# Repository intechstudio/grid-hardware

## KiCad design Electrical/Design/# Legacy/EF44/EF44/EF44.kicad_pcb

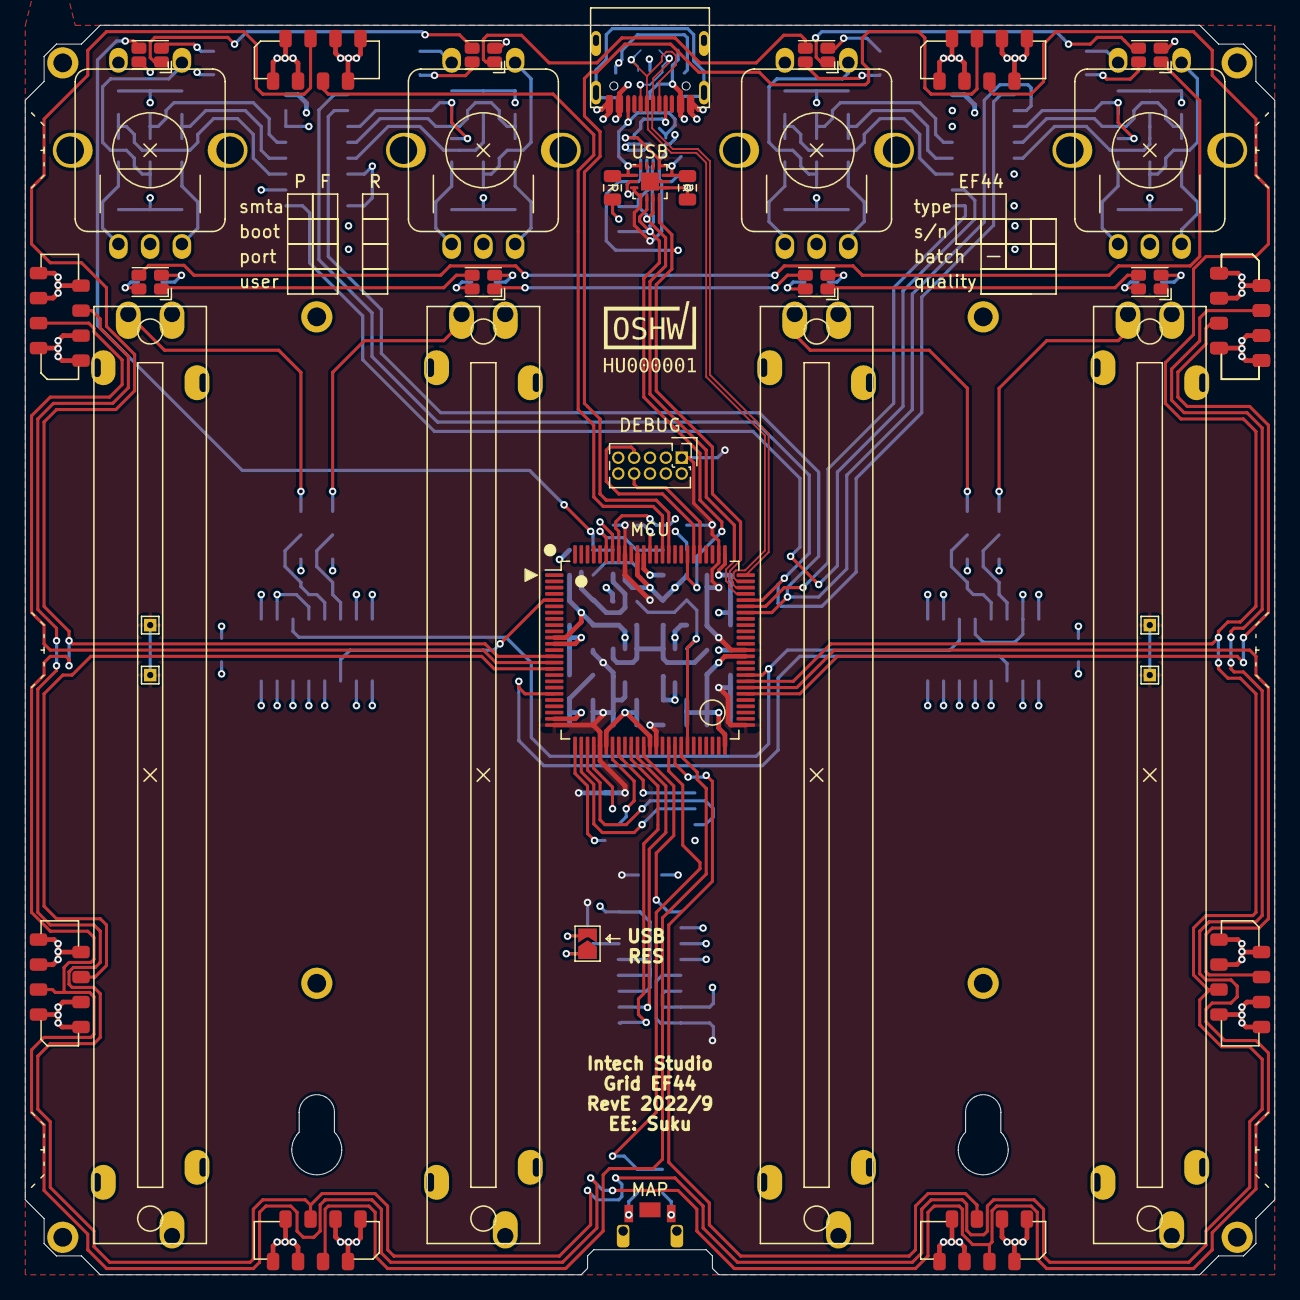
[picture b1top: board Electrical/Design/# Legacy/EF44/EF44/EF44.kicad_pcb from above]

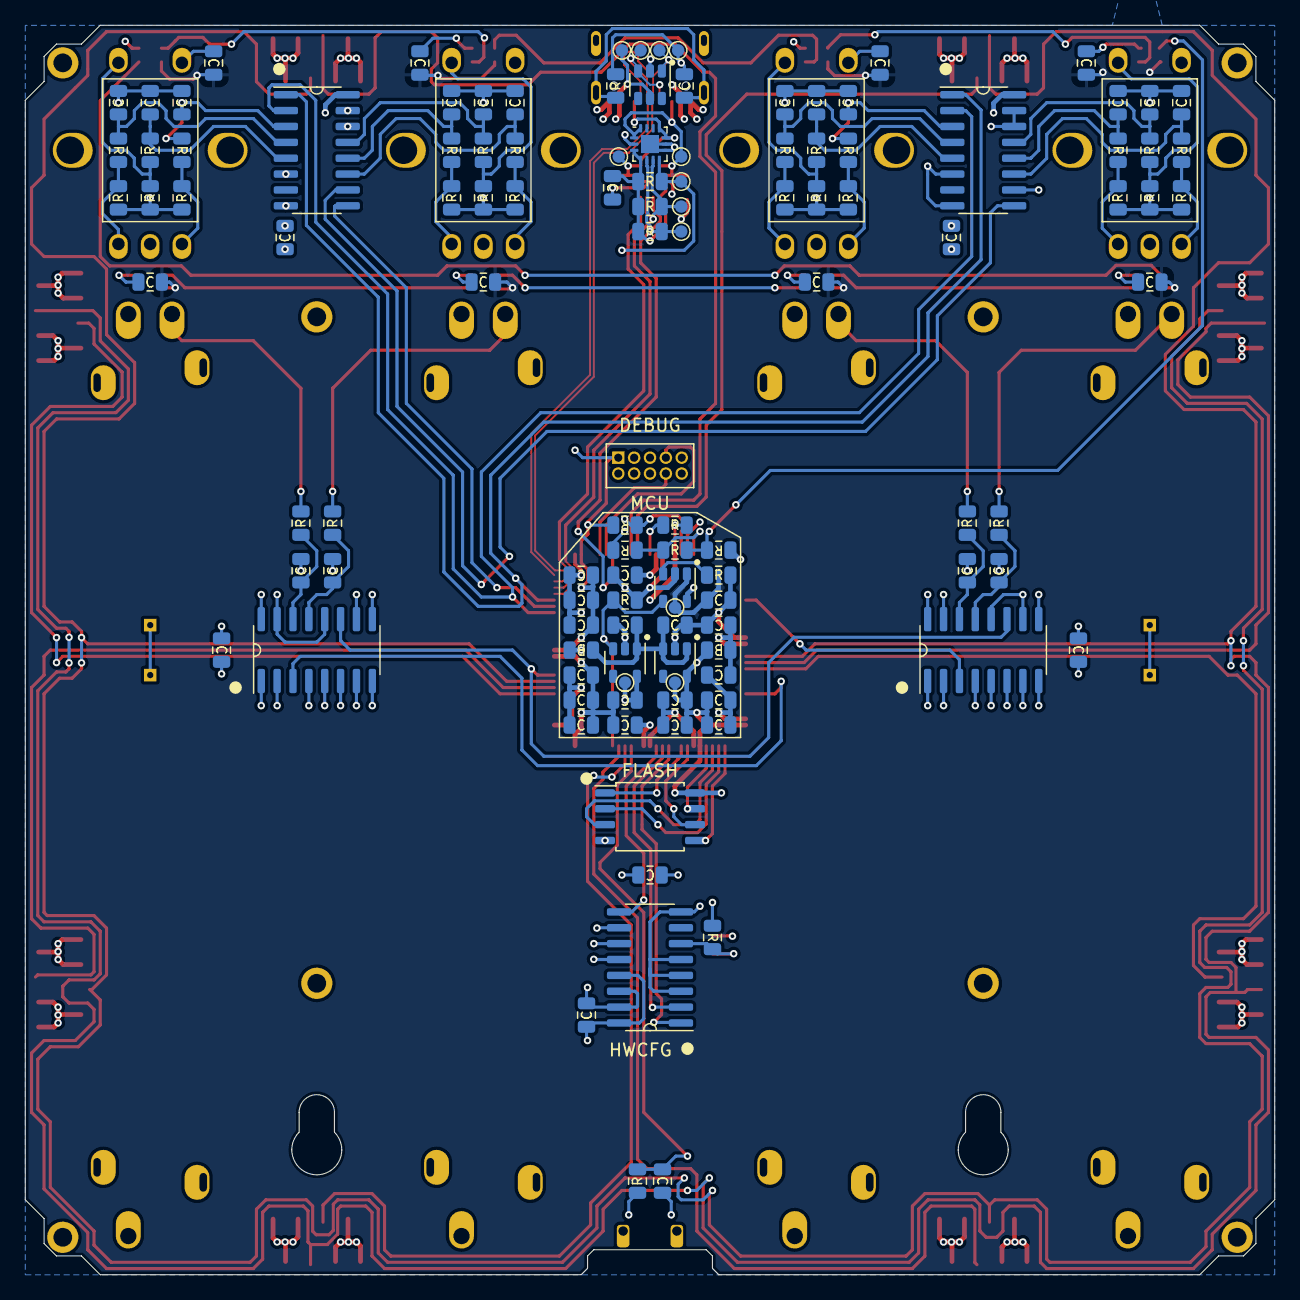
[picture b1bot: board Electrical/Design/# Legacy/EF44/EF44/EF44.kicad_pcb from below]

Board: 4 copper layers, 100.0 x 100.0 mm, 156 parts (117 on the bottom side), 94 nets.

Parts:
C1, C2, C3, C4, C5, C6, C7, C8, C9, C10, C11, C12, C13, C14, C17, C18, C19, C20, C21, C22, C23, C24, C25, C26, C27, C28, C33, C39, C41, C42, C44, C45, C46, C47, C48, C49, C51, C54, C55, C86, C87, C94, C95: 100n; CAP_0805
C34, C36, C40, C50, C53: 1u; CAP_0805
C37: 4n7; CAP_0805
C38, C43: 10u; CAP_0805
D1, D2, D3, D4, D5, D6, D7, D8: WS2812C-2020; UI_WS2812C-2020
J1: USB_C_TYPE-C-32-M-12; USB_C_Korean_Hroparts_TYPE-C-31-M-12
J2: (NF); PinHeader_2x05_P1.27mm_Vertical
J4, J5, J6, J7, J7#2, J8, J9, J10, J11: TE Connectivity 84982-8; grid_ffc_8_vertical_smd
JP2: (NF); SolderJumper-2_P1.3mm_Open_TrianglePad1.0x1.5mm
L1, L2: GZ2012D601TF; FERRIT_0805
LOGO1: OSHWA
M1: (NF); grid_outline
R1, R2, R3, R4, R5, R6, R7, R8, R9, R10, R11, R12, R13, R14, R15, R16, R17, R18, R19, R20, R21, R22, R23, R24, R36, R111, R112: 10k; RES_0805
R25, R26, R27, R28, R38, R39, R40, R41, R42: 1k; RES_0805
R34, R37, R107, R108, R109, R110: 5k1; RES_0805
R35: 1M; RES_0805
SW1: C255807; SW_HYP_MAPMODE
TP1, TP2, TP3, TP4: TestPoint; TestPoint_THTPad_1.0x1.0mm_Drill0.5mm
TP5: D-; TestPoint_Pad_D1.0mm
TP6: D+; TestPoint_Pad_D1.0mm
TP7: GND; TestPoint_Pad_D1.0mm
TP8: VB; TestPoint_Pad_D1.0mm
TP9: UC; TestPoint_Pad_D1.0mm
TP10: UI; TestPoint_Pad_D1.0mm
TP11: UI_5V; TestPoint_Pad_D1.0mm
TP16: SDA; TestPoint_Pad_D1.0mm
TP17: SCL; TestPoint_Pad_D1.0mm
TP18: INT; TestPoint_Pad_D1.0mm
TP19: CC1; TestPoint_Pad_D1.0mm
TP20: CC2; TestPoint_Pad_D1.0mm
U1, U2, U3: 74HC165; SOIC-16_74HC165
U4: SESRV05-4; SOT-23-6
U5, U6: LN1134A332MR-G; SOT-23-5
U7: SAMD51N20A; TQFP-100_14x14mm_P0.5mm
U8: W25Q16JVSSIQ; SOIC-8W_FLASH
U9, U10: 74HC4051; SOIC-16_74HC4051
U15, U16: FUSB302BMPX (NF); WQFN-14-1EP_2.5x2.5mm_P0.5mm_EP1.45x1.45mm
U17: MT9700; SOT-23-5
UI1, UI2, UI3, UI4: EN12-HS22AF20 (NF); UI_ENCODER_TT
UI5, UI6, UI7, UI8: PS60-10MC1BR10K (NF); UI_FADER_TT_long

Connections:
+3V3_UC: C33.1, C40.1, C41.1, C42.1, C43.1, C44.1, C45.1, C46.1, C47.1, C48.1, C51.1, C54.1, C55.1, C94.1, J2.1, L1.2, R38.2, R39.2, R108.1, R109.1, R110.1, R112.1, TP1.1, TP2.1, TP3.1, TP4.1, TP9.1, U3.13 (D2), U3.16 (VCC), U5.5 (OUT), U7.25 (VDDIOB0), U7.30 (VDDIOB1), U7.39 (VDDIO0), U7.51 (VDDIO1), U7.63 (VDDIO2), U7.77 (VDDIO3), U7.92 (VDDIO4), U8.8 (VCC), U15.3 (VDD), U15.4 (VDD), U16.3 (VDD), U16.4 (VDD)
+3V3_UI: C13.1, C14.1, C36.1, C86.1, C87.1, R1.1, R2.1, R3.1, R7.1, R8.1, R9.1, R13.1, R14.1, R15.1, R19.1, R20.1, R21.1, TP10.1, U1.16 (VCC), U2.16 (VCC), U6.5 (OUT), U9.16 (VDD), U10.16 (VDD), UI5.1, UI6.1, UI7.1, UI8.1
+5V: J1.A4B9 (VBUS), J1.A9B4 (VBUS), J4.6, J4.7, J4.8, J5.1, J5.2, J5.3, J6.1, J6.2, J6.3, J7.6, J7.7, J7.8, J7#2.6, J7#2.7, J7#2.8, J8.6, J8.7, J8.8, J9.1, J9.2, J9.3, J10.1, J10.2, J10.3, J11.6, J11.7, J11.8, L2.2, R34.1, TP8.1, U4.5, U15.2 (VBUS), U16.2 (VBUS), U17.5 (IN)
+5V_UI: C1.2, C2.2, C3.2, C4.2, C5.2, C6.2, C7.2, C8.2, C50.1, D1.4 (VDD), D2.4 (VDD), D3.4 (VDD), D4.4 (VDD), D5.4 (VDD), D6.4 (VDD), D7.4 (VDD), D8.4 (VDD), TP11.1, U17.1 (OUT)
/HWCFG/HWCFG_CLOCK: U3.2 (CLK), U7.36 (PB14)
/HWCFG/HWCFG_DATA: U3.9 (Q), U7.37 (PB15)
/HWCFG/HWCFG_SHIFT: U3.1 (SH/~LD), U7.35 (PB13)
/MCU/GRID_AUX_RX: J2.8, U7.80 (PB24)
/MCU/GRID_AUX_TX: J2.7, U7.81 (PB25)
/MCU/GRID_EAST_RX: J7.5, J7#2.5, U7.56 (PC16)
/MCU/GRID_EAST_TX: J9.4, U7.57 (PC17)
/MCU/GRID_NORTH_RX: J4.5, U7.86 (PC28)
/MCU/GRID_NORTH_TX: J5.4, U7.85 (PC27)
/MCU/GRID_SOUTH_RX: J11.5, U7.42 (PC12)
/MCU/GRID_SOUTH_TX: J10.4, U7.43 (PC13)
/MCU/GRID_SYNC_1: J5.5, J6.5, J9.5, J10.5, U7.58 (PC18)
/MCU/GRID_SYNC_2: J4.4, J7.4, J7#2.4, J8.4, J11.4, U7.14 (PB07)
/MCU/GRID_WEST_RX: J8.5, U7.16 (PB09)
/MCU/GRID_WEST_TX: J6.4, U7.15 (PB08~)
/MCU/LED_DATA_OUT: D1.3 (DIN), R34.2, R42.2
/MCU/MAP_MODE: C95.1, R40.2, U7.41 (PC11)
/MCU/MUX_ADDRESS_A: U7.59 (PC19), U9.11 (A), U10.11 (A)
/MCU/MUX_OUT_1: U7.5 (PC02), U9.3 (X)
/MCU/MUX_OUT_2: U7.20 (PA07), U10.3 (X)
/MCU/QSPI_IO_0: U7.26 (PA08), U8.5 (DI(IO0))
/MCU/QSPI_IO_1: U7.27 (PA09), U8.2 (DO(IO1))
/MCU/QSPI_IO_2: U7.28 (PA10), U8.3 (IO2)
/MCU/QSPI_IO_3: U7.29 (PA11), U8.7 (IO3)
/MCU/QSPI_SCK: U7.32 (PB10), U8.6 (CLK)
/MCU/QSPI_~CE: U7.33 (PB11), U8.1 (~CS)
/MCU/SYS_I2C_INT_0: R110.2, TP18.1, U7.82 (PC24), U15.5 (INT_N), U16.5 (INT_N)
/MCU/SYS_I2C_SCL: R109.2, TP17.1, U7.72 (PA22), U15.6 (SCL), U16.6 (SCL)
/MCU/SYS_I2C_SDA: R108.2, TP16.1, U7.73 (PA23), U15.7 (SDA), U16.7 (SDA)
/MCU/SYS_RESET: J2.10, R38.1, U7.88 (~RESET)
/MCU/SYS_SWCLK: J2.4, R39.1, U7.93 (PA30)
/MCU/SYS_SWDIO: J2.2, U7.94 (PA31)
/MCU/SYS_SWO: J2.6, R41.2
/MCU/Sheet60FB6C45/USB_CC1: J1.A5 (CC1), R37.1, TP19.1, U15.10 (CC1), U15.11 (CC1), U16.10 (CC1), U16.11 (CC1)
/MCU/Sheet60FB6C45/USB_CC2: J1.B5 (CC2), R107.1, TP20.1, U15.1 (CC2), U15.14 (CC2), U16.1 (CC2), U16.14 (CC2)
/MCU/UI_PWR_EN: R36.1, U6.3 (EN), U7.44 (PC14), U17.4 (ON)
/MCU/USB_DN: J1.A7 (D-), J1.B7 (D-), TP5.1, U4.1, U7.74 (PA24)
/MCU/USB_DP: J1.A6 (D+), J1.B6 (D+), TP6.1, U4.3, U7.75 (PA25)
/UI_ENC/CLOCK: U1.2 (CLK), U2.2 (CLK), U7.69 (PB21)
/UI_ENC/DATA: U2.9 (Q), U7.70 (PA20)
/UI_ENC/ENCODER_1/A: C19.1, R6.1, U1.11 (D0)
/UI_ENC/ENCODER_1/B: C18.1, R5.1, U1.12 (D1)
/UI_ENC/ENCODER_1/C: C17.1, R4.2, U1.13 (D2)
/UI_ENC/ENCODER_2/A: C22.1, R12.1, U1.3 (D4)
/UI_ENC/ENCODER_2/B: C21.1, R11.1, U1.4 (D5)
/UI_ENC/ENCODER_2/C: C20.1, R10.2, U1.5 (D6)
/UI_ENC/ENCODER_3/A: C25.1, R18.1, U2.11 (D0)
/UI_ENC/ENCODER_3/B: C24.1, R17.1, U2.12 (D1)
/UI_ENC/ENCODER_3/C: C23.1, R16.2, U2.13 (D2)
/UI_ENC/ENCODER_4/A: C28.1, R24.1, U2.3 (D4)
/UI_ENC/ENCODER_4/B: C27.1, R23.1, U2.4 (D5)
/UI_ENC/ENCODER_4/C: C26.1, R22.2, U2.5 (D6)
/UI_ENC/SHIFT: U1.1 (SH/~LD), U2.1 (SH/~LD), U7.71 (PA21)
GND: C1.1, C2.1, C3.1, C4.1, C5.1, C6.1, C7.1, C8.1, C9.2, C10.2, C11.2, C12.2, C13.2, C14.2, C17.2, C18.2, C19.2, C20.2, C21.2, C22.2, C23.2, C24.2, C25.2, C26.2, C27.2, C28.2, C33.2, C34.2, C36.2, C37.2, C38.2, C39.2, C40.2, C41.2, C42.2, C43.2, C44.2, C45.2, C46.2, C47.2, C48.2, C49.2, C50.2, C51.2, C53.2, C54.2, C55.2, C86.2, C87.2, C94.2, C95.2, D1.2 (VSS), D2.2 (VSS), D3.2 (VSS), D4.2 (VSS), D5.2 (VSS), D6.2 (VSS), D7.2 (VSS), D8.2 (VSS), J1.A1B12 (GND), J1.A12B1 (GND), J2.3, J2.5, J2.9, J4.1, J4.2, J4.3, J5.6, J5.7, J5.8, J6.6, J6.7, J6.8, J7.1, J7.2, J7.3, J7#2.1, J7#2.2, J7#2.3, J8.1, J8.2, J8.3, J9.6, J9.7, J9.8, J10.6, J10.7, J10.8, J11.1, J11.2, J11.3, JP2.2 (B), R35.2, R36.2, R37.2, R107.2, R111.2, SW1.2 (B), TP7.1, U1.6 (D7), U1.8 (GND), U1.10 (SI), U1.14 (D3), U1.15 (INH), U2.6 (D7), U2.8 (GND), U2.14 (D3), U2.15 (INH), U3.3 (D4), U3.4 (D5), U3.5 (D6), U3.8 (GND), U3.10 (SI), U3.11 (D0), U3.12 (D1), U3.14 (D3), U3.15 (INH), U4.2, U5.2 (GND), U6.2 (GND), U7.11 (GNDANA), U7.24 (GNDIOB0), U7.31 (GNDIOB0), U7.38 (GND0), U7.50 (GND1), U7.62 (GND2), U7.76 (GND3), U7.90 (GND4), U8.4 (GND), U9.1 (X4), U9.2 (X6), U9.4 (X7), U9.5 (X5), U9.6 (Inh), U9.7 (VEE), U9.8 (VSS), U9.9 (C), U9.10 (B), U9.12 (X3), U9.15 (X2), U10.1 (X4), U10.2 (X6), U10.4 (X7), U10.5 (X5), U10.6 (Inh), U10.7 (VEE), U10.8 (VSS), U10.9 (C), U10.10 (B), U10.12 (X3), U10.15 (X2), U15.8 (GND), U15.9 (GND), U15.15 (GND), U16.8 (GND), U16.9 (GND), U16.15 (GND), U17.2 (GND), UI1.2, UI1.4, UI2.2, UI2.4, UI3.2, UI3.4, UI4.2, UI4.4, UI5.3, UI6.3, UI7.3, UI8.3
unnamed: C9.1, R25.1, U9.13 (X0)
unnamed: C10.1, R26.1, U10.13 (X0)
unnamed: C11.1, R27.1, U9.14 (X1)
unnamed: C12.1, R28.1, U10.14 (X1)
unnamed: C34.1, C53.1, L2.1, U5.1 (IN), U5.3 (EN), U6.1 (IN)
unnamed: C37.1, J1.S1 (SHIELD), J1.S2 (SHIELD), R35.1
unnamed: C38.1, C39.1, L1.1, U7.12 (VDDANA)
unnamed: C49.1, U7.89 (VDDCORE)
unnamed: D1.1 (DOUT), D2.3 (DIN)
unnamed: D2.1 (DOUT), D3.3 (DIN)
unnamed: D3.1 (DOUT), D4.3 (DIN)
unnamed: D4.1 (DOUT), D5.3 (DIN)
unnamed: D5.1 (DOUT), D6.3 (DIN)
unnamed: D6.1 (DOUT), D7.3 (DIN)
unnamed: D7.1 (DOUT), D8.3 (DIN)
unnamed: JP2.1 (A), R112.2, U3.6 (D7)
unnamed: R1.2, R4.1, UI1.5
unnamed: R2.2, R5.2, UI1.3
unnamed: R3.2, R6.2, UI1.1
unnamed: R7.2, R10.1, UI2.5
unnamed: R8.2, R11.2, UI2.3
unnamed: R9.2, R12.2, UI2.1
unnamed: R13.2, R16.1, UI3.5
unnamed: R14.2, R17.2, UI3.3
unnamed: R15.2, R18.2, UI3.1
unnamed: R19.2, R22.1, UI4.5
unnamed: R20.2, R23.2, UI4.3
unnamed: R21.2, R24.2, UI4.1
unnamed: R25.2, UI5.2
unnamed: R26.2, UI7.2
unnamed: R27.2, UI6.2
unnamed: R28.2, UI8.2
unnamed: R40.1, SW1.1 (A)
unnamed: R41.1, R42.1, U7.95 (PB30)
unnamed: R111.1, U17.3 (SET)
unnamed: U1.9 (Q), U2.10 (SI)

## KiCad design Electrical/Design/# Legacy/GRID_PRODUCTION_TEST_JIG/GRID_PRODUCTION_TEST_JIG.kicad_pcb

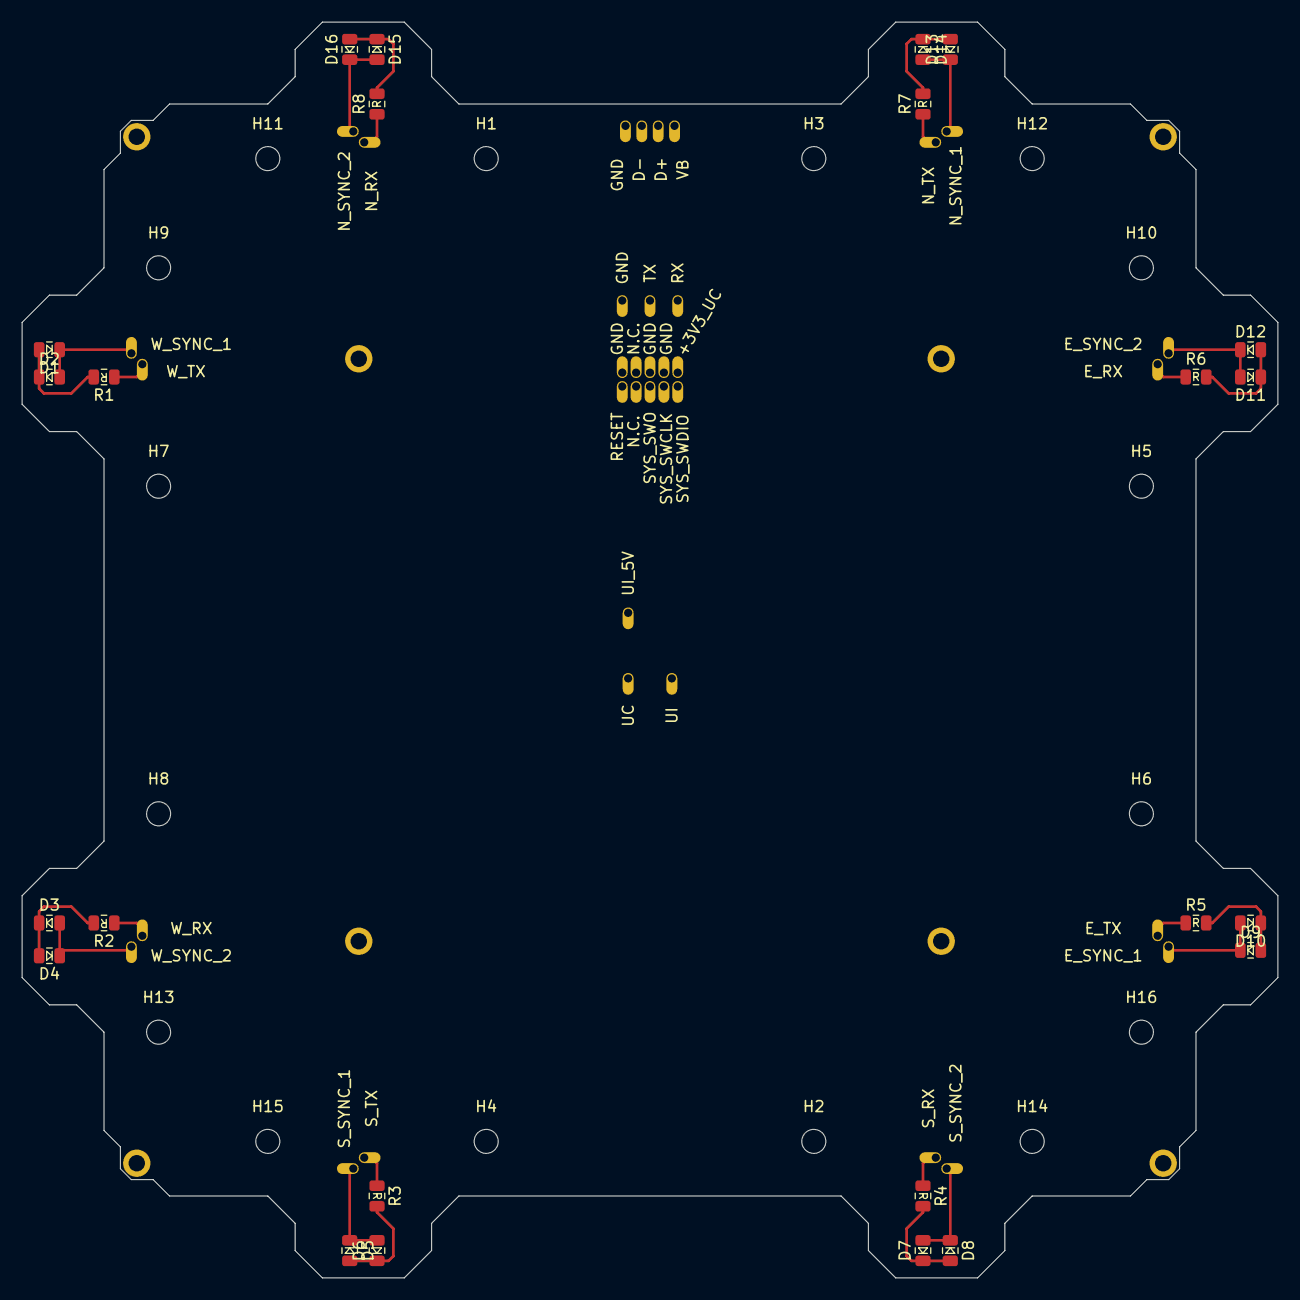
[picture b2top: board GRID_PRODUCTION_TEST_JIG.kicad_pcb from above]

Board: 2 copper layers, 115.0 x 115.0 mm, 77 parts (0 on the bottom side), 24 nets.

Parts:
D1, D2, D3, D4, D5, D6, D7, D8, D9, D10, D11, D12, D13, D14, D15, D16: LED; LED_0805
H1, H2, H3, H4, H5, H6, H7, H8, H9, H10, H11, H12, H13, H14, H15, H16: MountingHole; MountingHole_2.2mm_M2
M1: Conn_01x08; grid_outline
R1, R2, R3, R4, R5, R6, R7, R8: 1k; RES_0805
TP1: +3V3_UC; testpoint_pogo_0.75mm
TP2, TP3, TP5, TP11, TP18: GND; testpoint_pogo_0.75mm
TP4, TP9: N.C.; testpoint_pogo_0.75mm
TP6: SYS_SWDIO; testpoint_pogo_0.75mm
TP7: SYS_SWCLK; testpoint_pogo_0.75mm
TP8: SYS_SWO; testpoint_pogo_0.75mm
TP10: RESET; testpoint_pogo_0.75mm
TP12: VB; testpoint_pogo_0.75mm
TP13: D-; testpoint_pogo_0.75mm
TP14: D+; testpoint_pogo_0.75mm
TP15: UC; testpoint_pogo_0.75mm
TP16: UI; testpoint_pogo_0.75mm
TP17: UI_5V; testpoint_pogo_0.75mm
TP19: TX; testpoint_pogo_0.75mm
TP20: RX; testpoint_pogo_0.75mm
TP21: W_SYNC_1; testpoint_pogo_0.75mm
TP22: W_TX; testpoint_pogo_0.75mm
TP23: W_RX; testpoint_pogo_0.75mm
TP24: W_SYNC_2; testpoint_pogo_0.75mm
TP25: S_SYNC_1; testpoint_pogo_0.75mm
TP26: S_TX; testpoint_pogo_0.75mm
TP27: S_RX; testpoint_pogo_0.75mm
TP28: S_SYNC_2; testpoint_pogo_0.75mm
TP29: E_SYNC_1; testpoint_pogo_0.75mm
TP30: E_TX; testpoint_pogo_0.75mm
TP31: E_RX; testpoint_pogo_0.75mm
TP32: E_SYNC_2; testpoint_pogo_0.75mm
TP33: N_SYNC_1; testpoint_pogo_0.75mm
TP34: N_TX; testpoint_pogo_0.75mm
TP35: N_RX; testpoint_pogo_0.75mm
TP36: N_SYNC_2; testpoint_pogo_0.75mm

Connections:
unnamed: D1.1, D2.2, TP21.1
unnamed: D1.2, D2.1, R1.2
unnamed: D3.1, D4.2, R2.2
unnamed: D3.2, D4.1, TP24.1
unnamed: D5.1, D6.2, TP25.1
unnamed: D5.2, D6.1, R3.2
unnamed: D7.1, D8.2, R4.2
unnamed: D7.2, D8.1, TP28.1
unnamed: D9.2, D10.1, R5.2
unnamed: D9.1, D10.2, TP29.1
unnamed: D11.1, D12.2, R6.2
unnamed: D11.2, D12.1, TP32.1
unnamed: D13.1, D14.2, TP33.1
unnamed: D13.2, D14.1, R7.2
unnamed: D15.1, D16.2, R8.2
unnamed: D15.2, D16.1, TP36.1
unnamed: R1.1, TP22.1
unnamed: R2.1, TP23.1
unnamed: R3.1, TP26.1
unnamed: R4.1, TP27.1
unnamed: R5.1, TP30.1
unnamed: R6.1, TP31.1
unnamed: R7.1, TP34.1
unnamed: R8.1, TP35.1

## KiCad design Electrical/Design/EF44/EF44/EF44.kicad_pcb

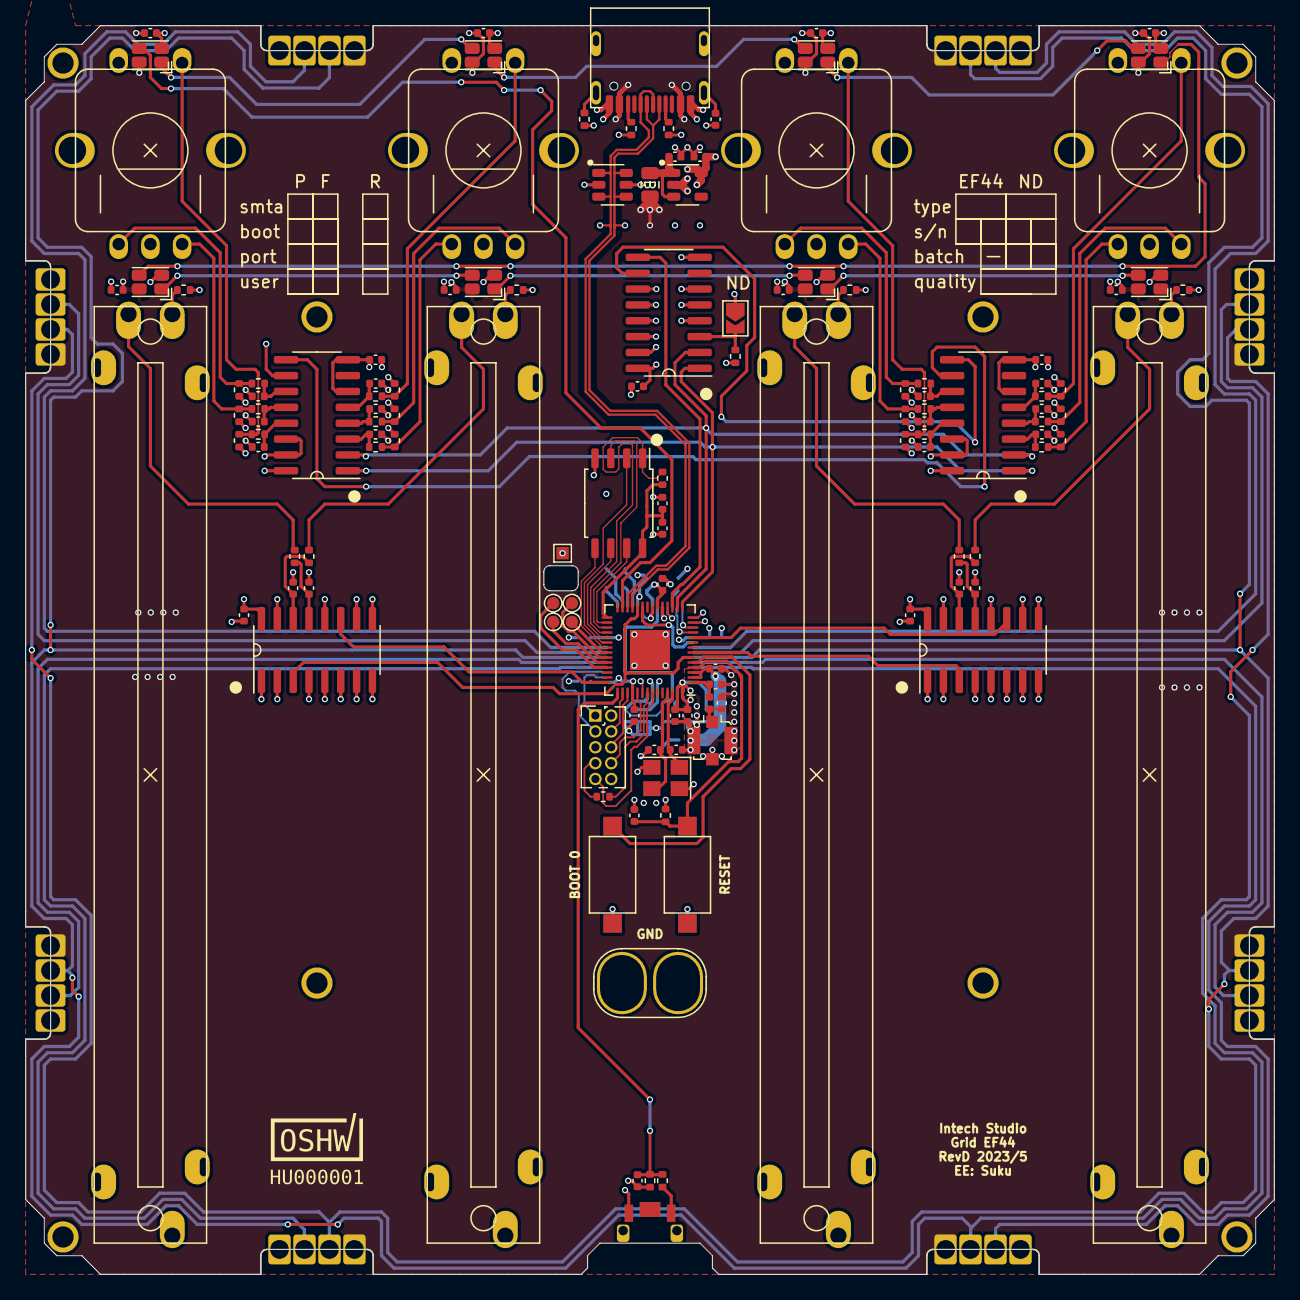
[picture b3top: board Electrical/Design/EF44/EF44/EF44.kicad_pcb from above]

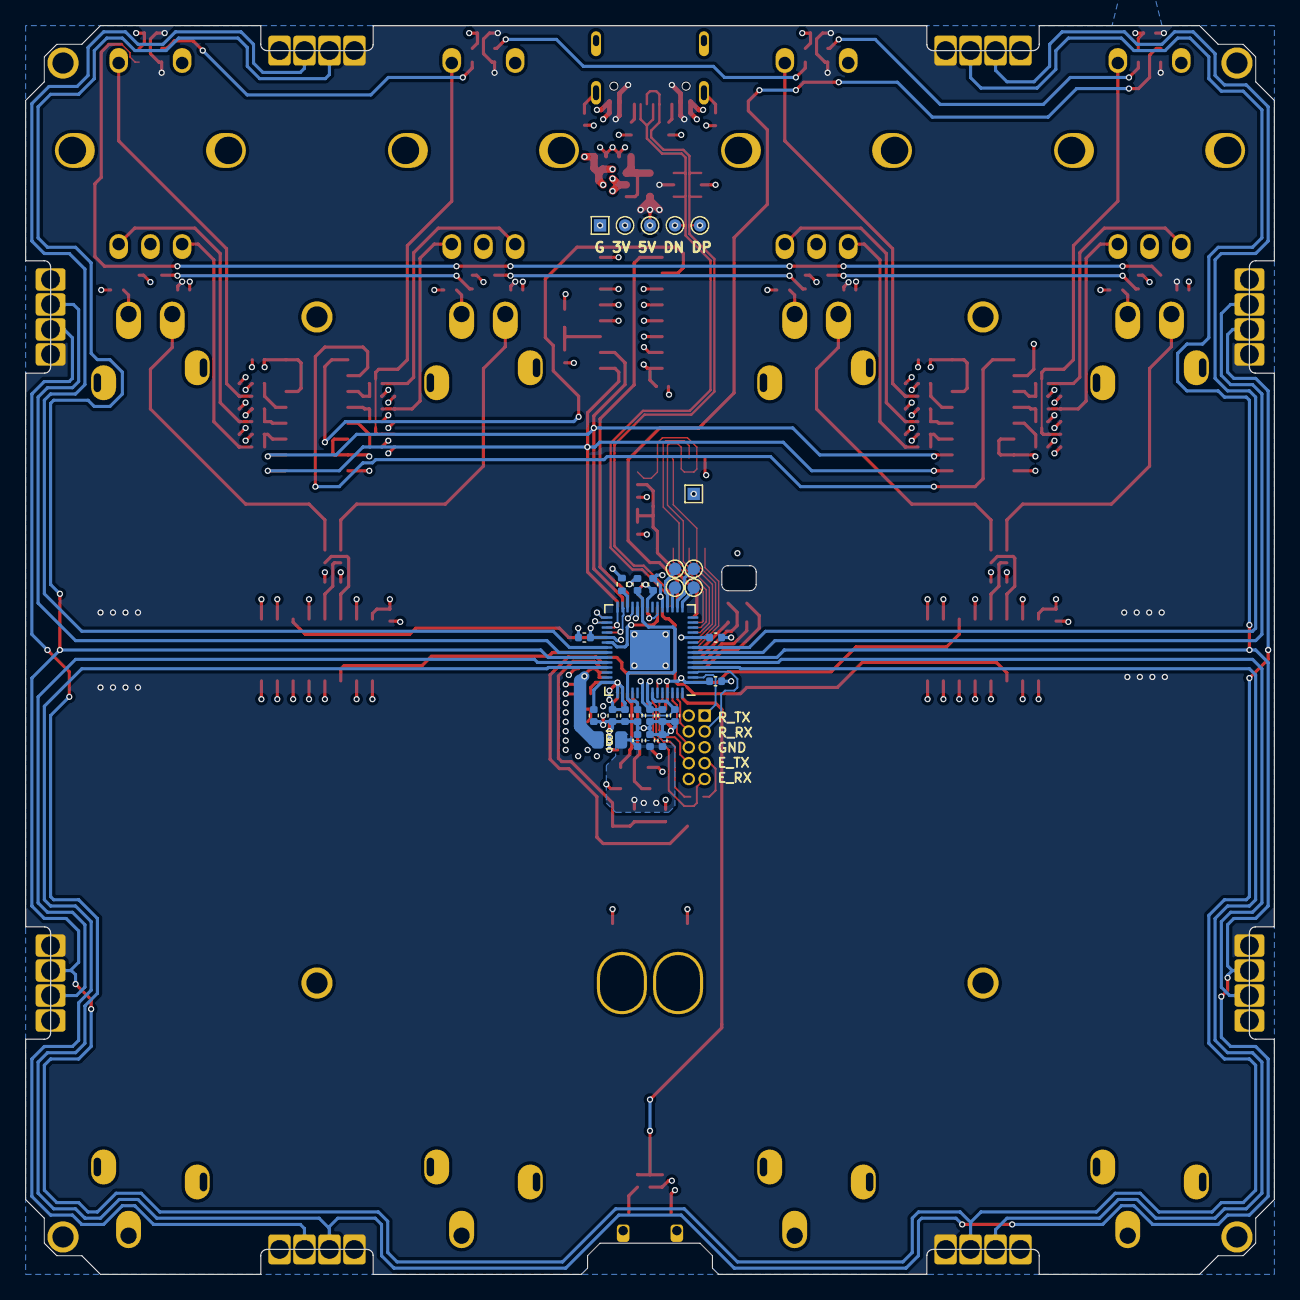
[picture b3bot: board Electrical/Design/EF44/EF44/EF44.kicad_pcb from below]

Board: 4 copper layers, 100.0 x 100.0 mm, 165 parts (28 on the bottom side), 117 nets.

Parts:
C731, C732, C735, C736, C737, C738, C740, C741, C744, C745, C747, C749, C751, C752, C756, C757, C801, C901, C902, C905, C906, C909, C910, C913, C914, C1001, C1002, C1003, C1004, C1005, C1006, C1013, C1014, C1015, C1019, C1023, C1027, C1028, C1029, C1030, C1031, C1032, C1048, C1049, C1050: 100n; CAP_0402
C733, C734, C746, C754, C755, C758, C760, C761: 1u; CAP_0402
C739: 3p9; CAP_0402
C742: 1p8; CAP_0402
C743: 10u; CAP_0402
C748, C750: 10p; CAP_0402
C753: 10n; CAP_0402
C759: 4n7; CAP_0402
D901, D902, D905, D906, D909, D910, D913, D914: WS2812C-2020; UI_WS2812C-2020
J701: Conn_Coaxial; U.FL_Molex_MCRF_73412-0110_Vertical
J702: (NF); PinHeader_2x05_P1.27mm_Vertical
J703, J704, J705, J706, J707, J708, J709, J710: AFB10-S08LCA-00; J_INTERFACE_SPRINGPATTERN
J711: USB_C_TYPE-C-32-M-12; USB_C_Korean_Hroparts_TYPE-C-31-M-12
J799: Conn_01x02; OscilloscopeGround
JP801: (NF); SolderJumper-2_P1.3mm_Open_TrianglePad1.0x1.5mm
L701: 1n8; IND_0402
L702, L703: GZ2012D601TF; FERRIT_0805
LOGO701: LOGO; OSHWA
M701: (NF); grid_outline
R701, R729, R734, R735, R738, R739, R801: 5k1; RES_0402
R733, R736, R1001, R1002, R1003, R1004: 1k; RES_0402
R737: 1M; RES_0402
R1005, R1006, R1007, R1008: 470R; RES_0402
R1025, R1026, R1027, R1028, R1029, R1030, R1037, R1038, R1039, R1040, R1041, R1042, R1043, R1044, R1045, R1046, R1047, R1048, R1079, R1080, R1081, R1082, R1083, R1084: 10k; RES_0402
SW701: C255807; SW_HYP_MAPMODE
SW702, SW703: C2905169; SW_SPST_CK_RS282G05A3
TP701, TP702, TP703, TP704, TP706, TP707, TP708, TP709: TestPoint; TestPoint_Pad_D1.0mm
TP705, TP710: TestPoint; TestPoint_Pad_1.0x1.0mm
TP711: GND; TestPoint_Pad_1.0x1.0mm
TP712: VB; TestPoint_Pad_D1.0mm
TP713: D-; TestPoint_Pad_D1.0mm
TP714: D+; TestPoint_Pad_D1.0mm
TP715: UI; TestPoint_Pad_D1.0mm
U703: RP2040; RP2040_QFN-56-1EP_7x7mm_P0.4mm_EP3.2x3.2mm
U704: ESP32-S3FN8; QFN-56-1EP_7x7mm_P0.4mm_EP3.2x3.2mm
U705: W25Q64JVSSIQ; SOIC-8W_FLASH
U706: SESRV05-4; SOT-23-6
U707: LN1134A332MR-G; SOT-23-5
U801, U1001, U1005: 74HC165; SOIC-16_74HC165
U1002, U1003: 74HC4051; SOIC-16_74HC4051
UI1001, UI1002, UI1003, UI1004: PS60-10MC1BR10K (NF); UI_FADER_TT_long
UI1005, UI1007, UI1008, UI1014: EN12-HS22AF20 (NF); UI_ENCODER_TT
Y701: ESP32_XTAL; Crystal_SMD_Abracon_ABM8G-4Pin_3.2x2.5mm

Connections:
+1V1: C731.1, C732.1, C733.1, U703.23 (DVDD), U703.45 (VREG_VOUT), U703.50 (DVDD)
+3V3: C734.1, C735.1, C736.1, C737.1, C738.1, C740.1, C741.1, C743.1, C744.1, C745.1, C746.1, C747.1, C751.1, C752.1, C753.1, C754.1, C757.2, C761.2, C801.1, C1003.1, C1006.1, C1019.1, C1023.1, JP801.1 (A), L702.2, R701.1, R729.1, R735.1, R1005.1, R1006.1, R1007.1, R1008.1, R1026.1, R1027.1, R1028.1, R1038.1, R1039.1, R1040.1, R1044.1, R1045.1, R1046.1, R1080.1, R1081.1, R1082.1, TP715.1, U703.1 (IOVDD), U703.10 (IOVDD), U703.22 (IOVDD), U703.33 (IOVDD), U703.42 (IOVDD), U703.43 (ADC_AVDD), U703.44 (VREG_IN), U703.48 (USB_VDD), U703.49 (IOVDD), U704.20 (VDD3P3_RTC), U704.46 (VDD3P3_CPU), U704.55 (VDDA1), U704.56 (VDDA2), U707.5 (OUT), U801.6 (D7), U801.13 (D2), U801.16 (VCC), U1001.16 (VCC), U1002.16 (VDD), U1003.16 (VDD), U1005.16 (VCC)
+5V: C901.2, C902.2, C905.2, C906.2, C909.2, C910.2, C913.2, C914.2, D901.4 (VDD), D902.4 (VDD), D905.4 (VDD), D906.4 (VDD), D909.4 (VDD), D910.4 (VDD), D913.4 (VDD), D914.4 (VDD), J703.4, J704.1, J705.1, J706.4, J707.4, J708.1, J709.1, J710.4, J711.A4B9 (VBUS), J711.A9B4 (VBUS), L703.2, TP712.1, U706.5
/HWCFG/HWCFG_DATA: U704.17 (GPIO12), U801.9 (Q)
/MCU/ESP_BOOT0: SW703.2 (B), U704.5 (GPIO0)
/MCU/ESP_LNA: C742.1, L701.2, U704.1 (LNA_IN)
/MCU/ESP_RESET: C758.1, R735.2, SW702.2 (B), U704.4 (CHIP_PU)
/MCU/GRID_EAST_RX: J709.3, U703.36 (GPIO24)
/MCU/GRID_EAST_TX: J710.2, U703.38 (GPIO26_ADC0)
/MCU/GRID_NORTH_RX: J705.3, U703.8 (GPIO6)
/MCU/GRID_NORTH_TX: J707.2, U703.35 (GPIO23)
/MCU/GRID_SOUTH_RX: J708.3, U703.39 (GPIO27_ADC1)
/MCU/GRID_SOUTH_TX: J706.2, U703.4 (GPIO2)
/MCU/GRID_SYNC_1: J703.3, J706.3, J707.3, J710.3, U703.37 (GPIO25)
/MCU/GRID_SYNC_2: J704.2, J705.2, J708.2, J709.2, U703.6 (GPIO4)
/MCU/GRID_WEST_RX: J704.3, U703.5 (GPIO3)
/MCU/GRID_WEST_TX: J703.2, U703.7 (GPIO5)
/MCU/LED_DATA_OUT: D901.3 (DIN), U704.27 (GPIO21)
/MCU/MAP_MODE: C757.1, R701.2, R736.2, U704.43 (GPIO38)
/MCU/RP_CLK: U703.20 (XIN), U704.21 (GPIO15)
/MCU/RP_INTERRUPT: U703.34 (GPIO22), U704.23 (GPIO17)
/MCU/RP_RUN: R729.2, U703.26 (RUN)
/MCU/RP_SPI0_CS: U703.28 (GPIO17), U704.12 (GPIO7)
/MCU/RP_SPI0_RX: U703.27 (GPIO16), U704.11 (GPIO6)
/MCU/RP_SPI0_SCK: U703.29 (GPIO18), U704.14 (GPIO9)
/MCU/RP_SPI0_TX: U703.30 (GPIO19), U704.13 (GPIO8)
/MCU/RP_SWCLK: U703.24 (SWCLK), U704.19 (GPIO14)
/MCU/RP_SWDIO: U703.25 (SWD), U704.18 (GPIO13)
/MCU/RP_UART0_RX: J702.3, U703.3 (GPIO1)
/MCU/RP_UART0_TX: J702.1, U703.2 (GPIO0)
/MCU/SPICLK: U704.33 (GPIO30), U705.6 (CLK)
/MCU/SPICS0: R734.2, U704.32 (GPIO29), U705.1 (~CS)
/MCU/SPID: U704.35 (GPIO32), U705.5 (DI(IO0))
/MCU/SPIHD: U704.30 (GPIO27), U705.7 (IO3)
/MCU/SPIQ: U704.34 (GPIO31), U705.2 (DO(IO1))
/MCU/SPIWP: U704.31 (GPIO28), U705.3 (IO2)
/MCU/TCK: J702.4, U704.44 (GPIO39)
/MCU/TDI: J702.8, U704.47 (GPIO41)
/MCU/TDO: J702.6, U704.45 (GPIO40)
/MCU/TMS: J702.2, U704.48 (GPIO42)
/MCU/U0RXD: J702.9, U704.50 (GPIO44)
/MCU/U0TXD: R733.2, U704.49 (GPIO43)
/MCU/USB_DN: J711.A7 (D-), J711.B7 (D-), TP713.1, U704.25 (GPIO19), U706.4, U706.6
/MCU/USB_DP: J711.A6 (D+), J711.B6 (D+), TP714.1, U704.26 (GPIO20), U706.1, U706.3
/UI_ENC/CLOCK: U704.16 (GPIO11), U801.2 (CLK), U1001.2 (CLK), U1005.2 (CLK)
/UI_ENC/DATA: U801.10 (SI), U1005.9 (Q)
/UI_ENC/ENCODER_0/A: C1015.1, R1030.1, U1001.11 (D0)
/UI_ENC/ENCODER_0/B: C1014.1, R1029.1, U1001.12 (D1)
/UI_ENC/ENCODER_0/C: C1013.1, R1025.2, U1001.13 (D2)
/UI_ENC/ENCODER_1/A: C1032.1, R1048.1, U1001.3 (D4)
/UI_ENC/ENCODER_1/B: C1031.1, R1047.1, U1001.4 (D5)
/UI_ENC/ENCODER_1/C: C1030.1, R1043.2, U1001.5 (D6)
/UI_ENC/ENCODER_2/A: C1050.1, R1084.1, U1005.11 (D0)
/UI_ENC/ENCODER_2/B: C1049.1, R1083.1, U1005.12 (D1)
/UI_ENC/ENCODER_2/C: C1048.1, R1079.2, U1005.13 (D2)
/UI_ENC/ENCODER_3/A: C1029.1, R1042.1, U1005.3 (D4)
/UI_ENC/ENCODER_3/B: C1028.1, R1041.1, U1005.4 (D5)
/UI_ENC/ENCODER_3/C: C1027.1, R1037.2, U1005.5 (D6)
/UI_ENC/SHIFT: U704.15 (GPIO10), U801.1 (SH/~LD), U1001.1 (SH/~LD), U1005.1 (SH/~LD)
ESP_GPIO_1: U704.6 (GPIO1), U704.24 (GPIO18), U1002.3 (X)
ESP_GPIO_2: U704.7 (GPIO2), U1003.3 (X)
ESP_GPIO_5: U704.10 (GPIO5), U1003.11 (A)
ESP_GPIO_33: TP709.1, U704.38 (GPIO33)
ESP_GPIO_34: TP708.1, U704.39 (GPIO34)
ESP_GPIO_37: U704.42 (GPIO37), U1002.11 (A)
ESP_GPIO_47: TP706.1, U704.37 (GPIO47)
ESP_GPIO_48: TP707.1, U704.36 (GPIO48)
GND: C731.2, C732.2, C733.2, C734.2, C735.2, C736.2, C737.2, C738.2, C739.2, C740.2, C741.2, C742.2, C743.2, C744.2, C745.2, C746.2, C747.2, C748.2, C749.2, C750.2, C751.2, C752.2, C753.2, C754.2, C755.2, C756.2, C758.2, C759.2, C760.2, C761.1, C801.2, C901.1, C902.1, C905.1, C906.1, C909.1, C910.1, C913.1, C914.1, C1001.2, C1002.2, C1003.2, C1004.2, C1005.2, C1006.2, C1013.2, C1014.2, C1015.2, C1019.2, C1023.2, C1027.2, C1028.2, C1029.2, C1030.2, C1031.2, C1032.2, C1048.2, C1049.2, C1050.2, D901.2 (VSS), D902.2 (VSS), D905.2 (VSS), D906.2 (VSS), D909.2 (VSS), D910.2 (VSS), D913.2 (VSS), D914.2 (VSS), J701.2 (Ext), J702.5, J703.1, J704.4, J705.4, J706.1, J707.1, J708.4, J709.4, J710.1, J711.A1B12 (GND), J711.A12B1 (GND), J799.1, J799.2, R737.2, R738.2, R739.2, R801.2, SW701.2 (B), SW702.1 (A), SW703.1 (A), TP705.1, TP710.1, TP711.1, U703.19 (TESTEN), U703.57 (GND), U704.57 (GND), U705.4 (GND), U706.2, U707.2 (GND), U801.4 (D5), U801.5 (D6), U801.8 (GND), U801.11 (D0), U801.12 (D1), U801.14 (D3), U801.15 (INH), U1001.6 (D7), U1001.8 (GND), U1001.10 (SI), U1001.14 (D3), U1001.15 (INH), U1002.1 (X4), U1002.2 (X6), U1002.4 (X7), U1002.5 (X5), U1002.6 (Inh), U1002.7 (VEE), U1002.8 (VSS), U1002.9 (C), U1002.10 (B), U1002.12 (X3), U1002.15 (X2), U1003.1 (X4), U1003.2 (X6), U1003.4 (X7), U1003.5 (X5), U1003.6 (Inh), U1003.7 (VEE), U1003.8 (VSS), U1003.9 (C), U1003.10 (B), U1003.12 (X3), U1003.15 (X2), U1005.6 (D7), U1005.8 (GND), U1005.14 (D3), U1005.15 (INH), UI1001.3, UI1002.3, UI1003.3, UI1004.3, UI1005.2, UI1005.4, UI1007.2, UI1007.4, UI1008.2, UI1008.4, UI1014.2, UI1014.4, Y701.2, Y701.4
unnamed: C749.1, L702.1, U704.2 (VDD3P3), U704.3 (VDD3P3)
unnamed: C759.1, J711.S1 (SHIELD)
unnamed: D901.1 (DOUT), D905.3 (DIN)
unnamed: D902.3 (DIN), D913.1 (DOUT)
unnamed: D902.1 (DOUT), D906.3 (DIN)
unnamed: D905.1 (DOUT), D909.3 (DIN)
unnamed: D906.1 (DOUT), D910.3 (DIN)
unnamed: D909.1 (DOUT), D913.3 (DIN)
unnamed: D910.1 (DOUT), D914.3 (DIN)
unnamed: C739.1, J701.1 (In), L701.1
unnamed: J702.7, R733.1
unnamed: J711.A5 (CC1), R738.1
unnamed: J711.B5 (CC2), R739.1
unnamed: J711.S2 (SHIELD), R737.1
unnamed: JP801.2 (B), R801.1, U801.3 (D4)
unnamed: R1001.2, UI1001.2
unnamed: R1002.2, UI1002.2
unnamed: R1003.2, UI1003.2
unnamed: R1004.2, UI1004.2
unnamed: R1005.2, UI1001.1
unnamed: R1006.2, UI1002.1
unnamed: R1007.2, UI1003.1
unnamed: R1008.2, UI1004.1
unnamed: R1025.1, R1026.2, UI1005.5
unnamed: R1027.2, R1029.2, UI1005.3
unnamed: R1028.2, R1030.2, UI1005.1
unnamed: R1037.1, R1038.2, UI1007.5
unnamed: R1039.2, R1041.2, UI1007.3
unnamed: R1040.2, R1042.2, UI1007.1
unnamed: R1043.1, R1044.2, UI1008.5
unnamed: R1045.2, R1047.2, UI1008.3
unnamed: R1046.2, R1048.2, UI1008.1
unnamed: R1079.1, R1080.2, UI1014.5
unnamed: R1081.2, R1083.2, UI1014.3
unnamed: R1082.2, R1084.2, UI1014.1
unnamed: R736.1, SW701.1 (A)
unnamed: TP701.1, U703.15 (GPIO12)
unnamed: TP702.1, U703.16 (GPIO13)
unnamed: TP703.1, U703.17 (GPIO14)
unnamed: TP704.1, U703.18 (GPIO15)
unnamed: C750.1, U704.53 (XTAL_N), Y701.3
unnamed: C748.1, U704.54 (XTAL_P), Y701.1
unnamed: C760.1, L703.1, U707.1 (IN), U707.3 (EN)
unnamed: U1001.9 (Q), U1005.10 (SI)
unnamed: C1001.1, R1001.1, U1002.13 (X0)
unnamed: C1002.1, R1002.1, U1002.14 (X1)
unnamed: C1004.1, R1003.1, U1003.13 (X0)
unnamed: C1005.1, R1004.1, U1003.14 (X1)
VDD_SPI: C755.1, C756.1, R734.1, U704.29 (VDD_SPI), U705.8 (VCC)
